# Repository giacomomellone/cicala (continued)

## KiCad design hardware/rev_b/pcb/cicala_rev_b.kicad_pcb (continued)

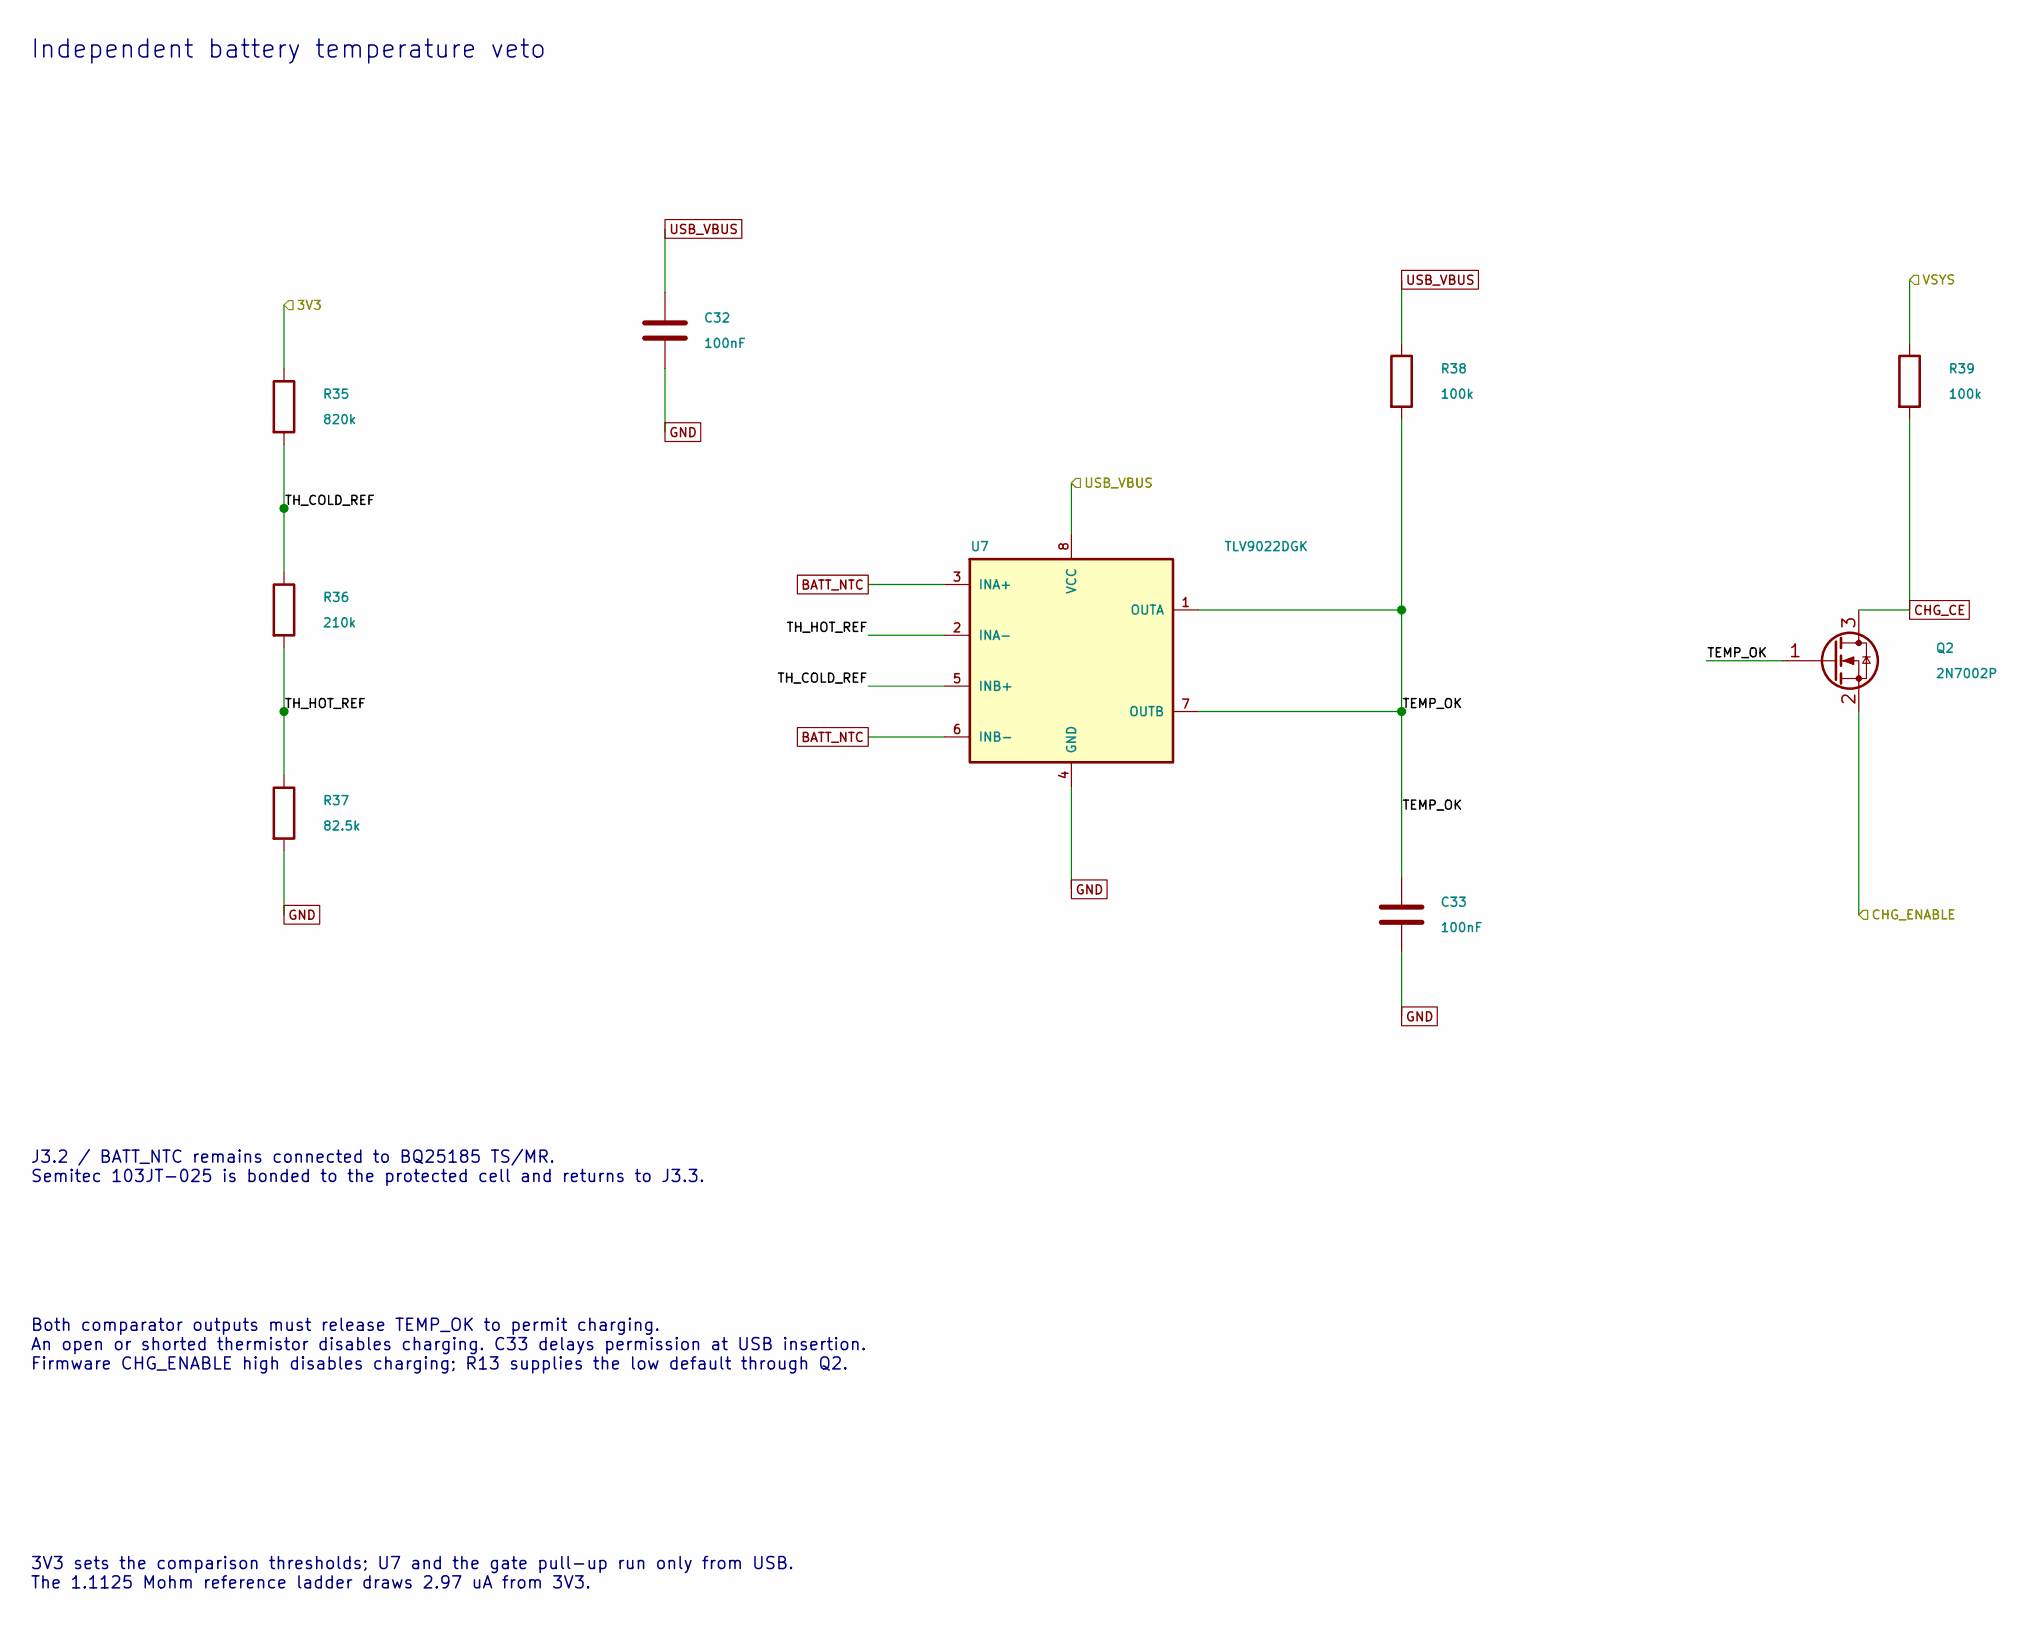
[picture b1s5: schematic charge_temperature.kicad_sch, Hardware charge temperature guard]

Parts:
C32, C33: 100nF; C_0603_1608Metric; MPN CL10B104KB8NNNC
Q2: 2N7002P; SOT-23; MPN 2N7002P,215
R35: 820k; R_0603_1608Metric; MPN RC0603FR-07820KL
R36: 210k; R_0603_1608Metric; MPN RC0603FR-07210KL
R37: 82.5k; R_0603_1608Metric; MPN RC0603FR-0782K5L
R38, R39: 100k; R_0603_1608Metric; MPN RC0603FR-07100KL
U7: TLV9022DGK; VSSOP-8_3x3mm_P0.65mm; MPN TLV9022DGKR

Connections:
3V3: R35.1; also elsewhere on the board
/Charge temperature guard/TEMP_OK: C33.1, Q2.1 (G), R38.2, U7.1 (OUTA), U7.7 (OUTB)
/Charge temperature guard/TH_COLD_REF: R35.2, R36.1, U7.5 (INB+)
/Charge temperature guard/TH_HOT_REF: R36.2, R37.1, U7.2 (INA-)
BATT_NTC: U7.3 (INA+), U7.6 (INB-); also elsewhere on the board
CHG_CE: Q2.3 (D), R39.2; also elsewhere on the board
CHG_ENABLE: Q2.2 (S); also elsewhere on the board
GND: C32.2, C33.2, R37.2, U7.4 (GND); also elsewhere on the board
USB_VBUS: C32.1, R38.1, U7.8 (VCC); also elsewhere on the board
VSYS: R39.1; also elsewhere on the board

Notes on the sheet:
Independent battery temperature veto
J3.2 / BATT_NTC remains connected to BQ25185 TS/MR. Semitec 103JT-025 is bonded to the protected cell and returns to J3.3.
Both comparator outputs must release TEMP_OK to permit charging. An open or shorted thermistor disables charging. C33 delays permission at USB insertion. Firmware CHG_ENABLE high disables charging; R13 supplies the low default through Q2.
3V3 sets the comparison thresholds; U7 and the gate pull-up run only from USB. The 1.1125 Mohm reference ladder draws 2.97 uA from 3V3.

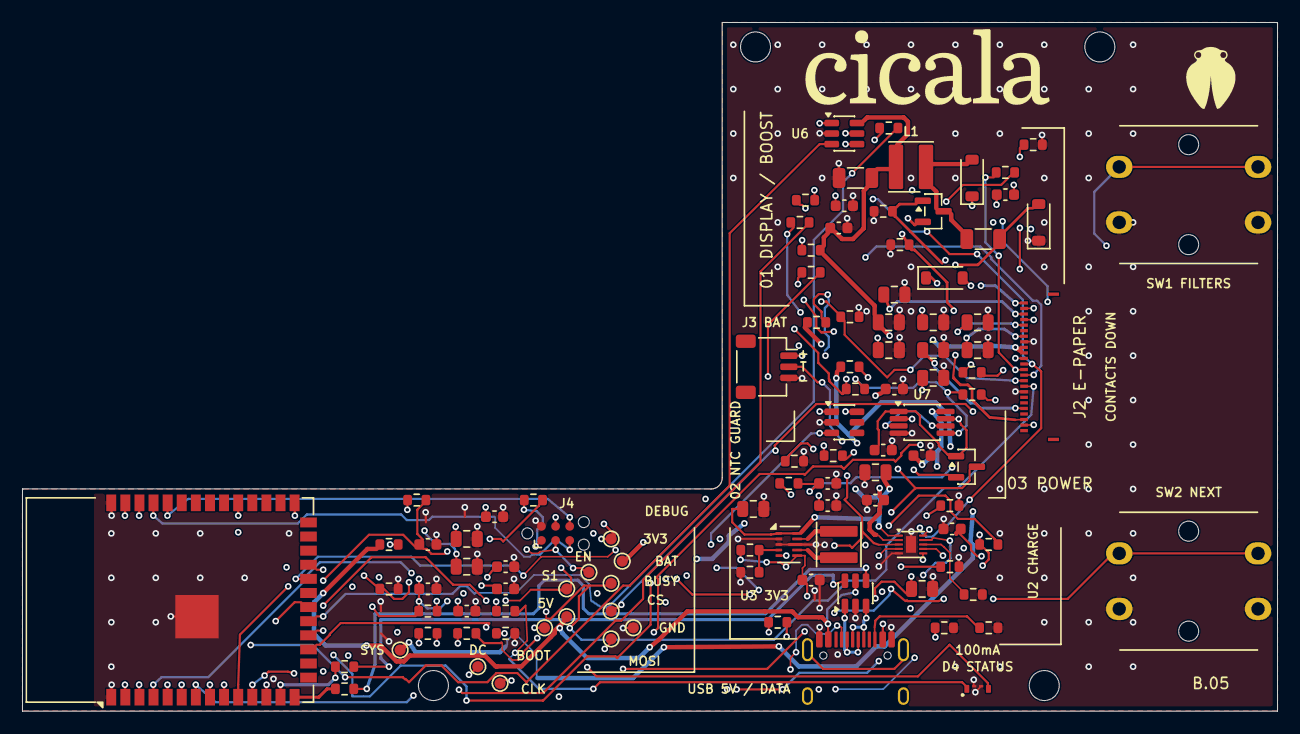
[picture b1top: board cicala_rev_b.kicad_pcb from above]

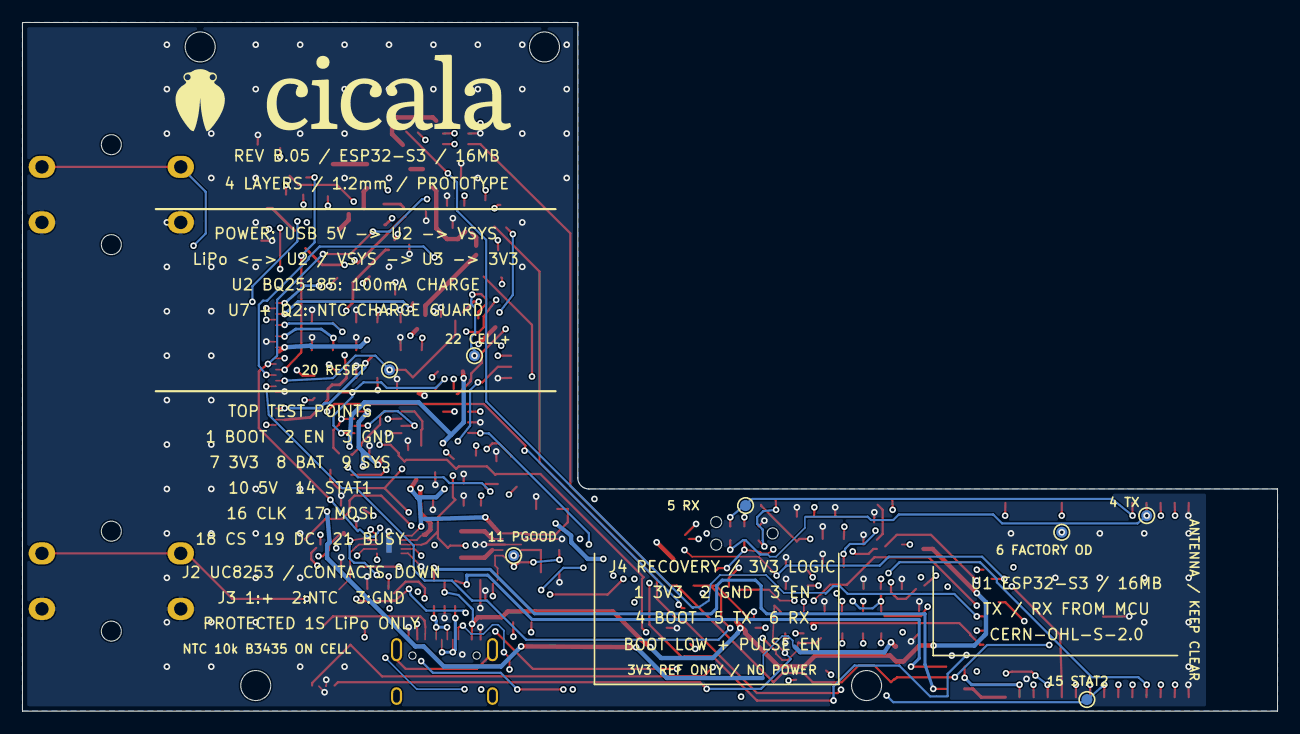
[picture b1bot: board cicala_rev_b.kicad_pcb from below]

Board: 4 copper layers, 113.0 x 62.0 mm, 115 parts (7 on the bottom side), 70 nets.

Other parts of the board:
H1, H2, H3, H4: M2.5; MountingHole_2.7mm

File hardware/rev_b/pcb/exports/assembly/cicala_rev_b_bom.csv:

"Refs","Value","Footprint","MPN","Manufacturer","LCSC","Qty","DNP"
"C3,C7,C11,C28,C32,C33","100nF","Capacitor_SMD:C_0603_1608Metric","CL10B104KB8NNNC","Samsung Electro-Mechanics","C1591","6",""
"C4,C6,C34","10uF 10V","Capacitor_SMD:C_0603_1608Metric","CL10A106KP8NNNC","Samsung Electro-Mechanics","C19702","3",""
"C5","10uF 25V","Capacitor_SMD:C_0805_2012Metric","CL21A106KAYNNNE","Samsung Electro-Mechanics","C15850","1",""
"C8,C10,C30","47uF 10V","Capacitor_SMD:C_0805_2012Metric","CL21A476MPYNNNE","Samsung Electro-Mechanics","C41796773","3",""
"C9","22uF 6.3V","Capacitor_SMD:C_0603_1608Metric","CL10A226MQ8NRNC","Samsung Electro-Mechanics","C59461","1",""
"C12,C27","1uF","Capacitor_SMD:C_0603_1608Metric","CL10B105KA8NNNC","Samsung Electro-Mechanics","C29936","2",""
"C13,C29","10uF","Capacitor_SMD:C_0603_1608Metric","CL10A106KP8NNNC","Samsung Electro-Mechanics","C19702","2",""
"C14","1nF","Capacitor_SMD:C_0603_1608Metric","CL10C102JB8NNNC","Samsung Electro-Mechanics","C163508","1",""
"C15,C16","4.7uF 50V","Capacitor_SMD:C_1206_3216Metric","GRM31CR71H475KA12L","Murata","","2",""
"C17-C24","1uF 50V","Capacitor_SMD:C_0805_2012Metric","CL21B105KBFNNNE","Samsung Electro-Mechanics","","8",""
"C25,C26","10nF","Capacitor_SMD:C_0603_1608Metric","CL10B103KB8NNNC","Samsung Electro-Mechanics","C1589","2",""
"D1-D3","MBR0530","Diode_SMD:D_SOD-123","MBR0530-7-F","Diodes Incorporated","","3",""
"D4","APBA2006SURKCGKC red/green","cicala:LED_Kingbright_APBA2006SURKCGKC","APBA2006SURKCGKC","Kingbright","","1",""
"J1","USB-C receptacle","cicala:USB_C_Receptacle_HRO_TYPE-C-31-M-12_EdgeOverhang","TYPE-C-31-M-12","HRO","","1",""
"J2","Waveshare 3.52in V1.1 UC8253","cicala:Molex_503480-2400_1x24_P0.5mm","503480-2400","Molex","","1",""
"J3","Battery + external 10k B3435 NTC","Connector_JST:JST_SH_SM03B-SRSS-TB_1x03-1MP_P1.00mm_Horizontal","SM03B-SRSS-TB(LF)(SN)","JST","","1",""
"L1","68uH","cicala:L_TDK_VLS4012","VLS4012CX-680M-1","TDK","","1",""
"L2","0.47uH XFL4015-471ME","cicala:L_Coilcraft_XFL4015","XFL4015-471ME","Coilcraft","","1",""
"Q1","BSS138","Package_TO_SOT_SMD:SOT-23","BSS138-7-F","Diodes Incorporated","","1",""
"Q2","2N7002P","Package_TO_SOT_SMD:SOT-23","2N7002P,215","Nexperia","","1",""
"R1,R2","5.1k","Resistor_SMD:R_0603_1608Metric","RC0603FR-075K1L","Yageo","","2",""
"R3,R4","22","Resistor_SMD:R_0603_1608Metric","RC0603FR-0722RL","Yageo","","2",""
"R5,R16,R38,R39","100k","Resistor_SMD:R_0603_1608Metric","RC0603FR-07100KL","Yageo","","4",""
"R6","150k","Resistor_SMD:R_0603_1608Metric","RC0603FR-07150KL","Yageo","","1",""
"R7","18k","Resistor_SMD:R_0603_1608Metric","RC0603FR-0718KL","Yageo","","1",""
"R8","3.00k","Resistor_SMD:R_0603_1608Metric","RC0603FR-073KL","Yageo","","1",""
"R9,R10,R19,R25,R26","10k","Resistor_SMD:R_0603_1608Metric","RC0603FR-0710KL","Yageo","","5",""
"R11,R32","1M","Resistor_SMD:R_0603_1608Metric","RC0603FR-071ML","Yageo","","2",""
"R12","470k","Resistor_SMD:R_0603_1608Metric","RC0603FR-07470KL","Yageo","","1",""
"R13","4.7k","Resistor_SMD:R_0603_1608Metric","RC0603FR-074K7L","Yageo","","1",""
"R14","511k 1%","Resistor_SMD:R_0603_1608Metric","RC0603FR-07511KL","Yageo","","1",""
"R15","91k 1%","Resistor_SMD:R_0603_1608Metric","RC0603FR-0791KL","Yageo","","1",""
"R18","150","Resistor_SMD:R_0603_1608Metric","RC0603FR-07150RL","Yageo","","1",""
"R20","3","Resistor_SMD:R_0603_1608Metric","RC0603FR-073RL","Yageo","","1",""
"R21,R22","22k","Resistor_SMD:R_0603_1608Metric","RC0603FR-0722KL","Yageo","","2",""
"R23,R24","1k","Resistor_SMD:R_0603_1608Metric","RC0603FR-071KL","Yageo","","2",""
"R27-R31","470","Resistor_SMD:R_0603_1608Metric","RC0603FR-07470RL","Yageo","","5",""
"R33,R34","0","Resistor_SMD:R_0603_1608Metric","RC0603JR-070RL","Yageo","","2",""
"R35","820k","Resistor_SMD:R_0603_1608Metric","RC0603FR-07820KL","Yageo","","1",""
"R36","210k","Resistor_SMD:R_0603_1608Metric","RC0603FR-07210KL","Yageo","","1",""
"R37","82.5k","Resistor_SMD:R_0603_1608Metric","RC0603FR-0782K5L","Yageo","","1",""
"SW1,SW2","B3F-4050","cicala:SW_Omron_B3F-4050","B3F-4050","Omron","","2",""
"U1","ESP32-S3-WROOM-1-N16","cicala:ESP32-S3-WROOM-1_NoEmbeddedVias","ESP32-S3-WROOM-1-N16","Espressif Systems","","1",""
"U2","BQ25185DLH","cicala:Texas_DLH0010A_NoEmbeddedVias","BQ25185DLHR","Texas Instruments","","1",""
"U3","TPS63802DLA","cicala:Texas_DLA0010A_VSON-HR-10_2x3mm_P0.5mm","TPS63802DLAR","Texas Instruments","","1",""
"U4","USBLC6-2SC6","Package_TO_SOT_SMD:SOT-23-6","USBLC6-2SC6","STMicroelectronics","","1",""
"U5,U6","TPS22917DBVR","Package_TO_SOT_SMD:SOT-23-6","TPS22917DBVR","Texas Instruments","","2",""
"U7","TLV9022DGK","Package_SO:VSSOP-8_3x3mm_P0.65mm","TLV9022DGKR","Texas Instruments","","1",""
